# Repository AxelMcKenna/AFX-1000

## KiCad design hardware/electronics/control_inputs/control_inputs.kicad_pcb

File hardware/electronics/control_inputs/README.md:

# E18 digital input hub

This 64 × 54 mm, four-layer board connects all32 front button/selector inputs
and four external-profile rear/status inputs to three MCP23017-E/SO expanders.
It uses the corrected [F04 mapping](../../firmware/control-inputs.json), leaving
GPA7/GPB7 unconnected because the manufacturer specifies them as output-only.
It is a prototype subassembly. Pots, LED/display drivers, touch electrodes,
angle sensing and physical validation remain open.

The native schematic has15 circuit components. Its independently checked
netlist, all-severity ERC/DRC, schematic parity and open-connection checks pass.
The saved PCB has424 segments,62 through vias and a filled inner AGND plane.
These checks establish the saved connectivity and design-rule result; they
do not establish real scan latency, signal integrity, EMC/ESD or physical fit.

The PCB sits at layout(109,43), seat Z=12.1mm, above the E19 processor
carrier on four nominal4mm spacers. Its four Ø2.4mm mounting holes are board-
relative(4,4),(60,4),(4,50),(60,50). Matching E19 processor-carrier holes and copper
keepouts are implemented. The 2mm left shift clears the lower fixing bounds.
Spacer OD≤5.5mm,
screw/washer OD≤5.5mm and head height≤2mm are assembly limits with no selected
parts or engagement proof. The placement packet uses actual PCB courtyards,
connector expansion0.5mm, an11mm connector/harness height allocation,≤3mm
trimmed THT protrusion including solder and stated board/seat allowances.
The A05 housing model includes the routed E19 carrier, lower fixing heads/nuts
and the daughterboard allocations. Complete wiring paths, exact fixing parts
and final electronics fit remain open.

| Header | Connection |
| --- | --- |
| J1,2×8 | Front inputs0–13; pin order follows the routed fanout; pins15/16 ground |
| J2,2×8 | Front inputs14–27; pins15/16 ground |
| J3,1×5 | Ground,Scene9,Default/User,Back Spin,Vinyl Brake |
| J4,1×5 | Ground,Send/Return sense,manual bypass sense,ANALOG_OK,INPUT_READY |
| J5,1×5 | Ground,shared MCU3.3V,SCL,SDA,CONTROL_RESET_N |

Use the [exported connector map](generated/connector-map.csv) for every pin and
logical control ID. J1/J2 alternate A-side reverse order with B-side forward
order; do not wire them as consecutive logical inputs. The connectors are
engineering pin-header footprints. Production connector, mating cable,
retention and polarity/keying selections remain unfinished.

**Connect J4 only with `PROFILE=external`.** Onboard firmware makes its GPA0..3
unused low outputs; leave J4 unplugged for onboard-codec bring-up. External
ANALOG_OK and INPUT_READY receive47kΩ/270kΩ pull-downs on this board and no
internal pull-ups. This implements the receiving loads required by E09/E11.
Both active-low rear switch inputs use the expander's configured pull-ups.

J5 reset is D0/CODEC_RUN externally or D27 onboard. R1 adds a receiving100kΩ
pull-down; this replaces the earlier prospective onboard reset pull-up.
F04 drives reset low then high and verifies direction/pull-up/output-latch
readback before accepting controls. Missing-drive, partial-power, leakage and
reset transients still need hardware qualification. A shared3.3V supply is
required; never power this board's logic from5V or join independent3.3V outputs.

There are no I²C pull-ups on E18. E09 R1/R2 supply the single2kΩ pair for the
external profile. Onboard bench bring-up needs an equivalent external pair.
Include fixed module pull-ups in the total bus load and measure rise time,
capacitance, ringing and actual scan cadence before accepting400kHz operation.
All switch leads remain inside the enclosure; system-level ESD/EMI provisions
and harness qualification are unfinished.

Regenerate and verify with the root [uv environment](../../../README.md#python-tooling)
and KiCad10.0.7:

```sh
uv run --locked python -m hardware.electronics.control_inputs.generate
uv run --locked python -m hardware.electronics.control_inputs.board --kicad-cli /path/to/kicad-cli
uv run --locked python -m hardware.electronics.control_inputs.verify --kicad-cli /path/to/kicad-cli
uv run --locked python -m hardware.cad.standalone
uv run --locked python -m hardware.cad.render --openscad /path/to/openscad
```

`board.py` uses explicit GPIO fanouts and a conservative grid-routing aid for
the remaining slow digital nets. Native KiCad DRC/parity checks the resulting
saved copper. `verify.py` independently declares all15 component contracts,
checks F04 logical/physical input mapping and NC-pad isolation, audits SOIC
pad numbering/positions, re-exports E09/E11 interfaces, and produces the
[verification record](generated/verification.json) and
[PCB placement packet](generated/placement.json). It uses shared parser and
transform helpers from E07; it does not import this board's circuit specification.

The MCP source is Microchip
[DS20001952D](https://ww1.microchip.com/downloads/aemDocuments/documents/APID/ProductDocuments/DataSheets/MCP23017-Data-Sheet-DS20001952.pdf).
Standard KiCad footprints are embedded in the board and hashed in the record.
Full manufacturer land-pattern/stencil approval, exact passive/connector MPNs,
fabrication stackup and physical performance are still pending. This board
does not complete the standalone unit or authorize a complete fabrication run.

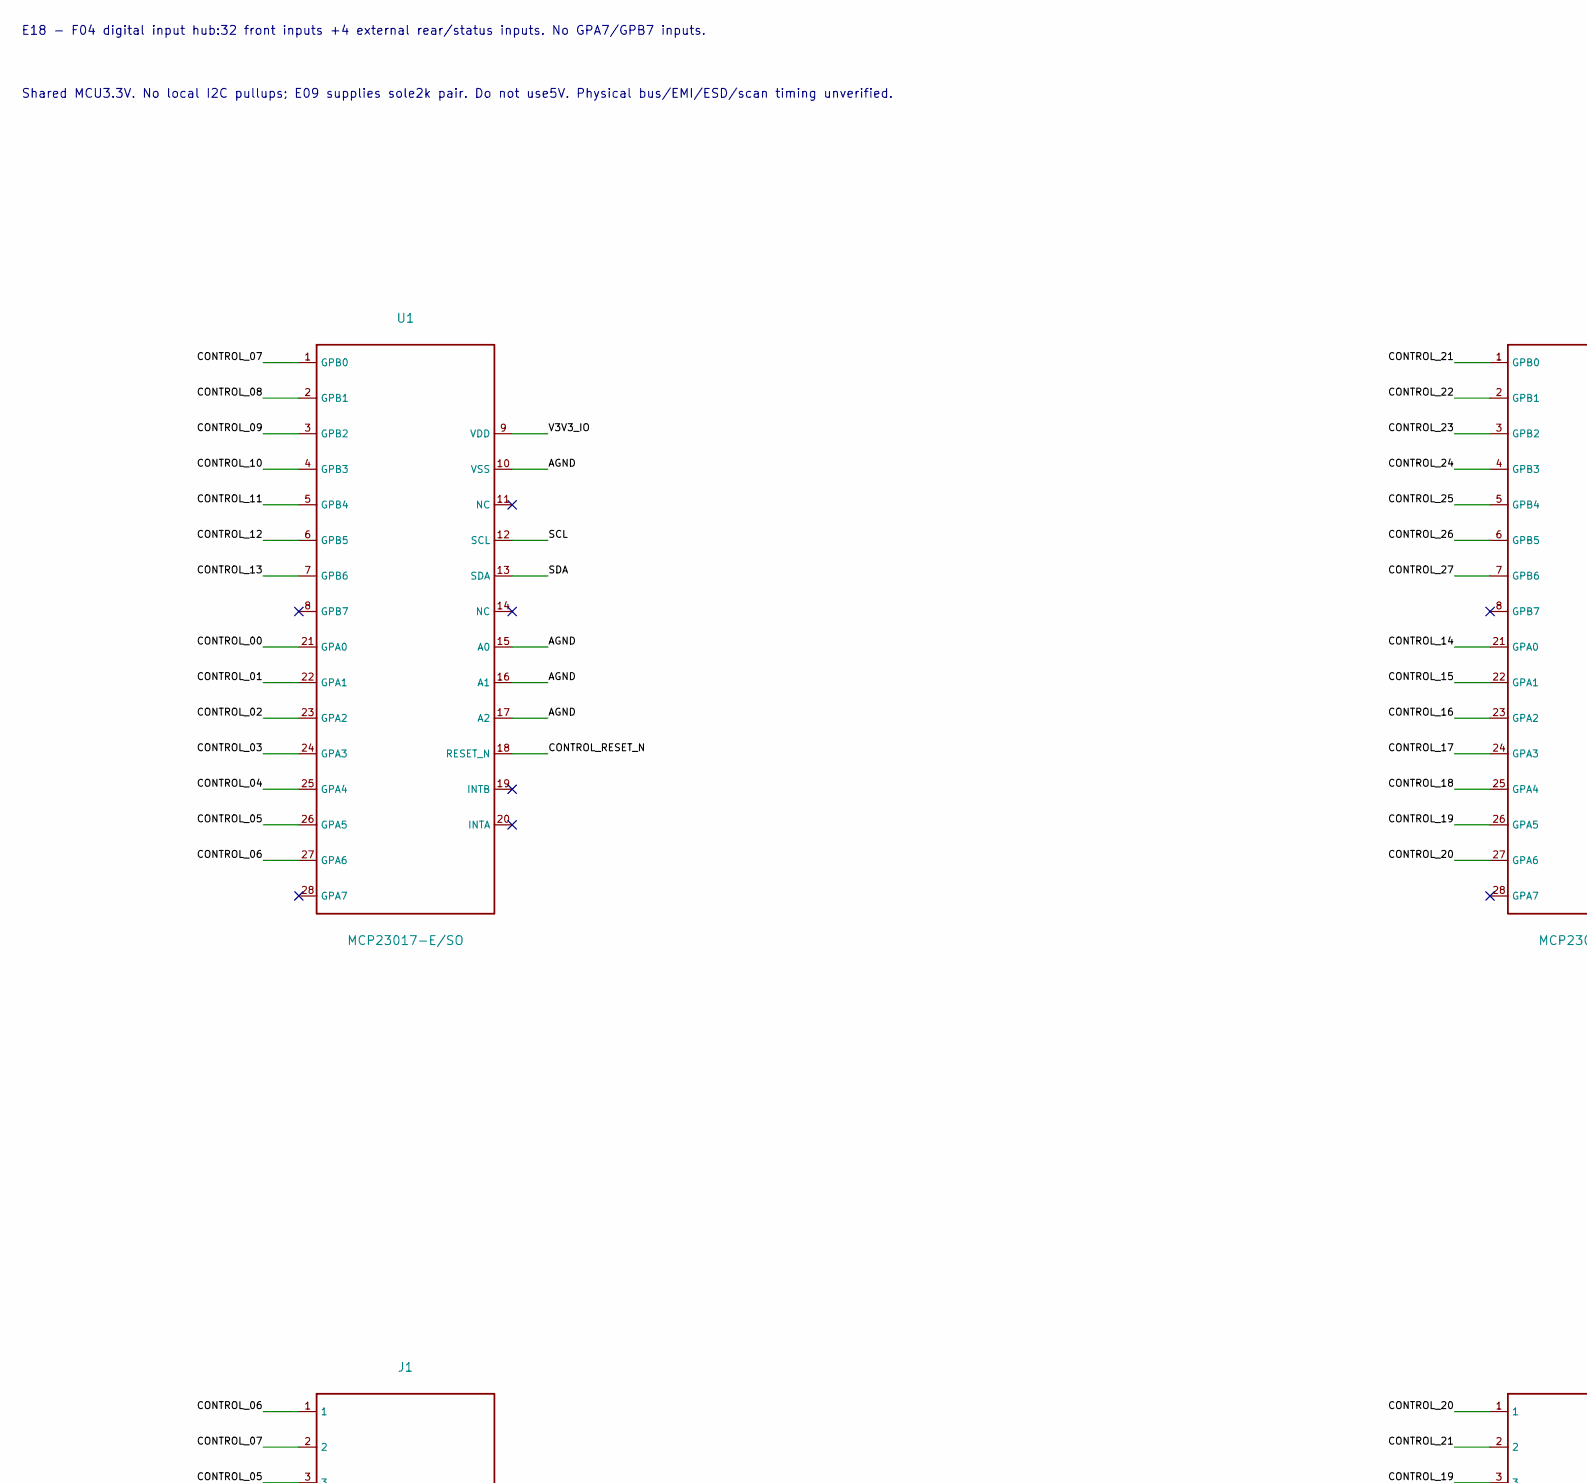
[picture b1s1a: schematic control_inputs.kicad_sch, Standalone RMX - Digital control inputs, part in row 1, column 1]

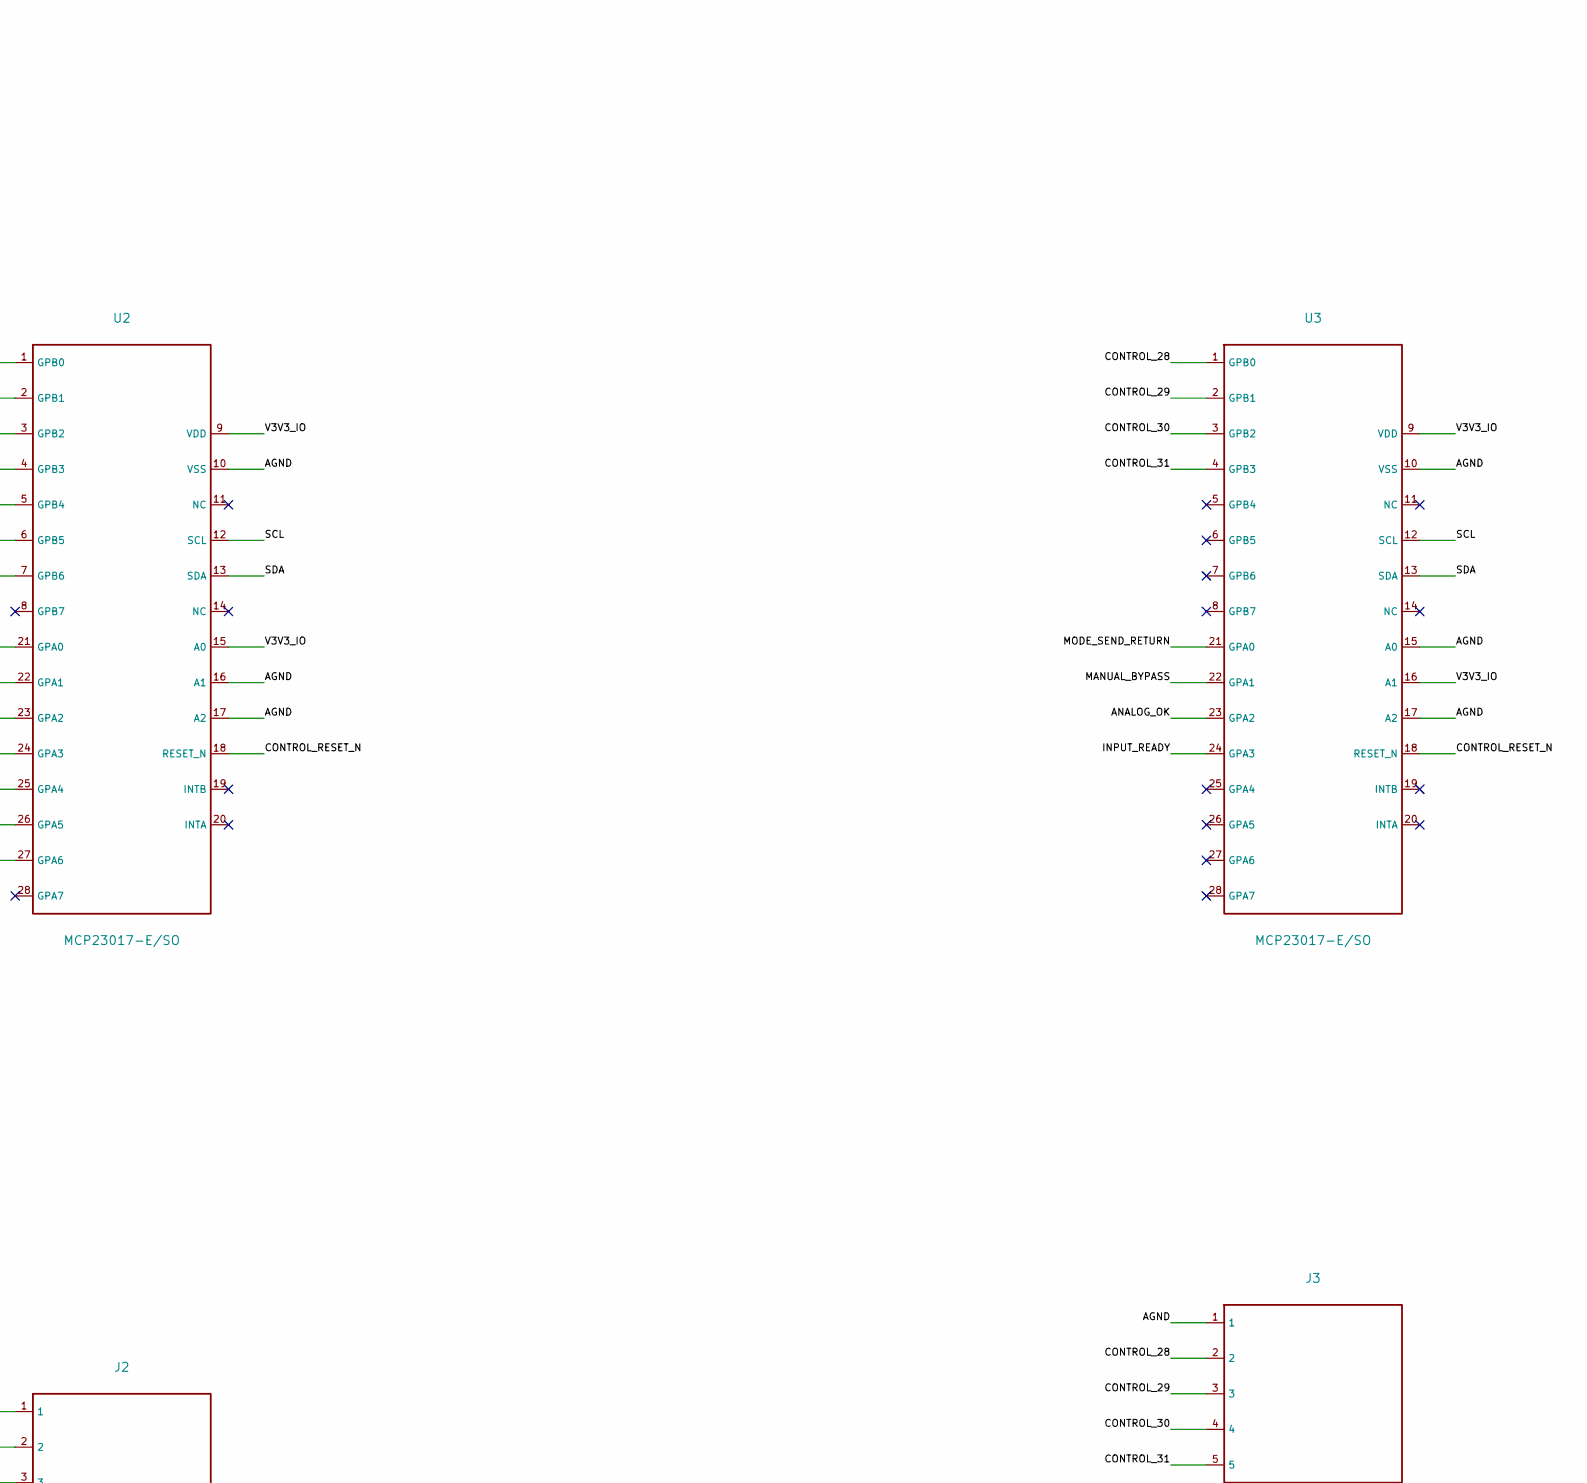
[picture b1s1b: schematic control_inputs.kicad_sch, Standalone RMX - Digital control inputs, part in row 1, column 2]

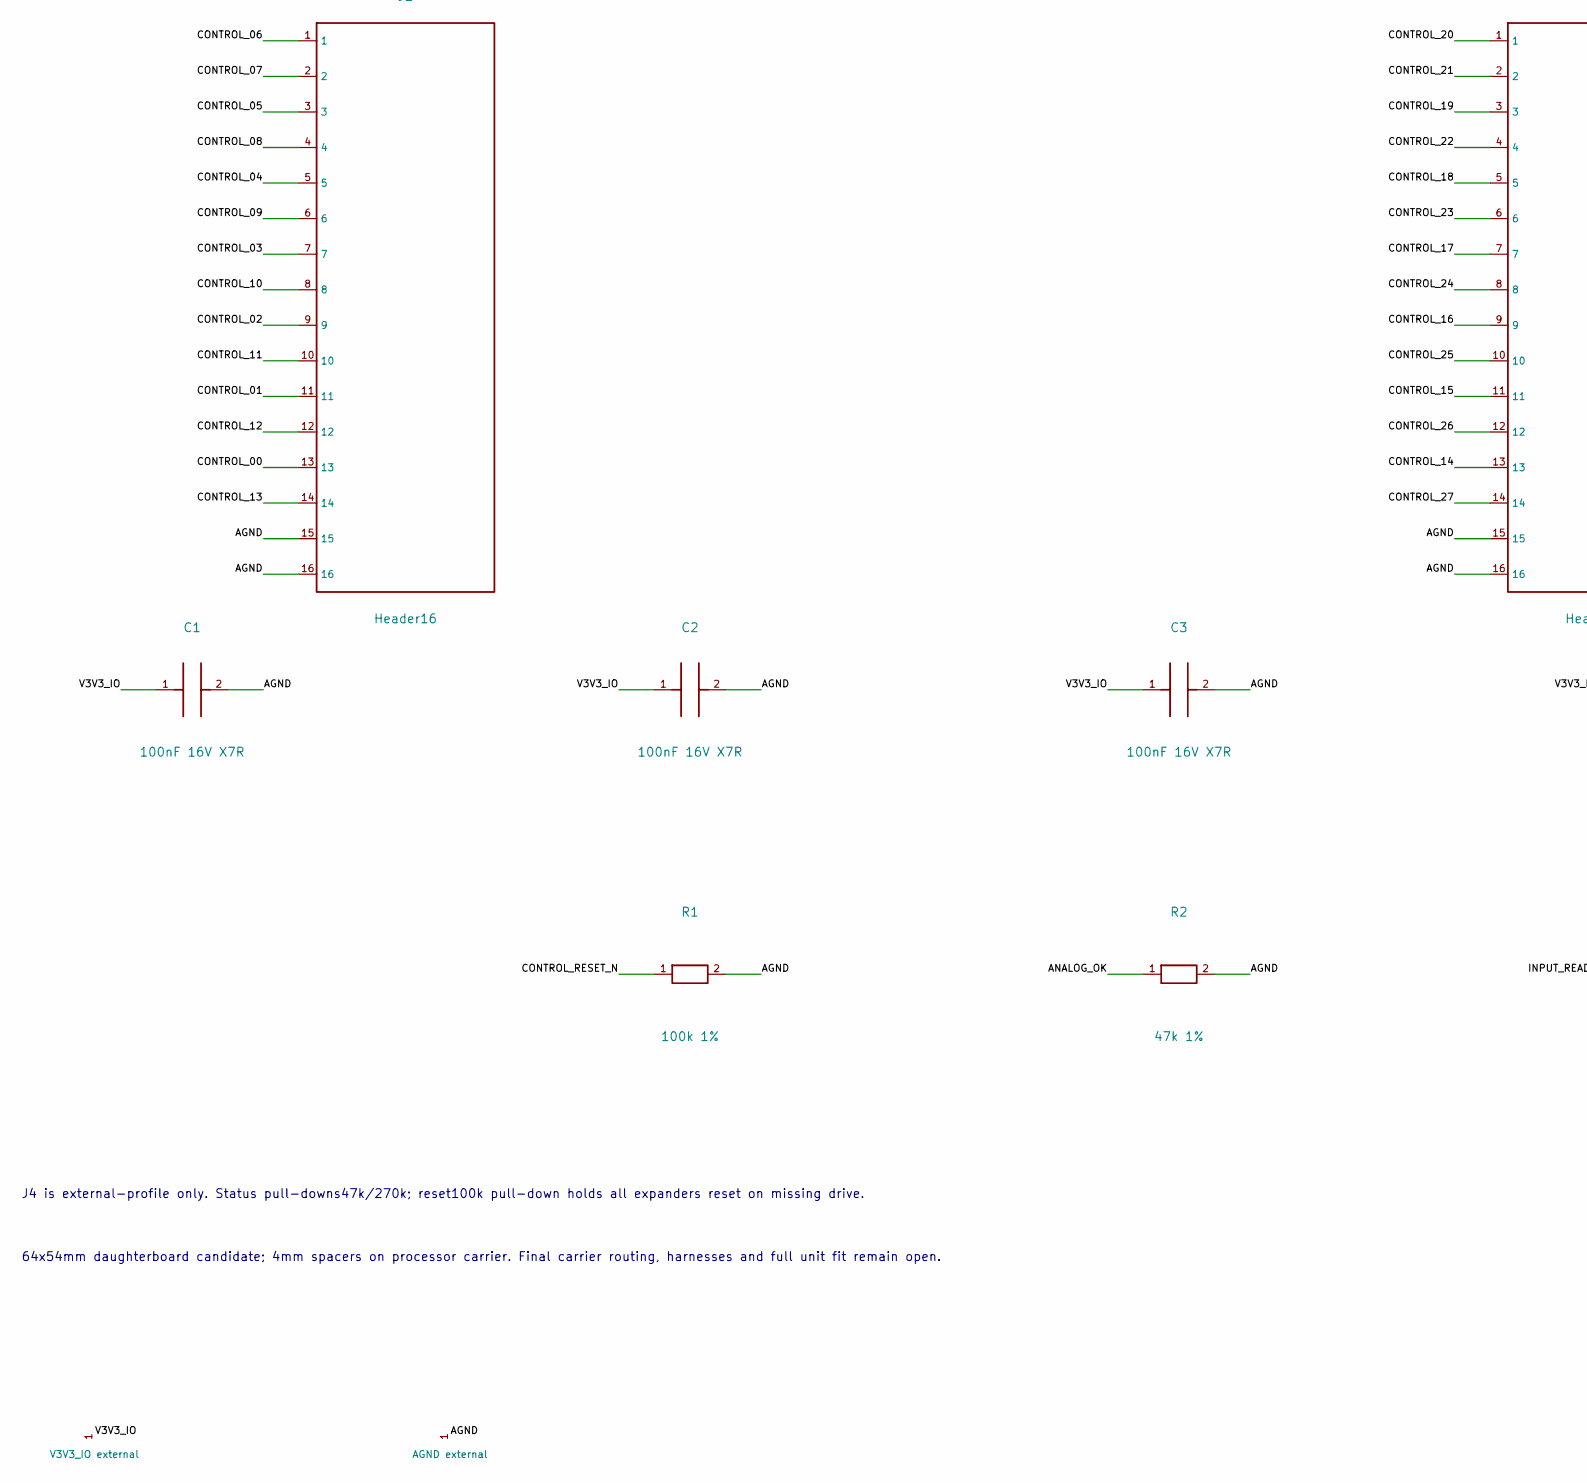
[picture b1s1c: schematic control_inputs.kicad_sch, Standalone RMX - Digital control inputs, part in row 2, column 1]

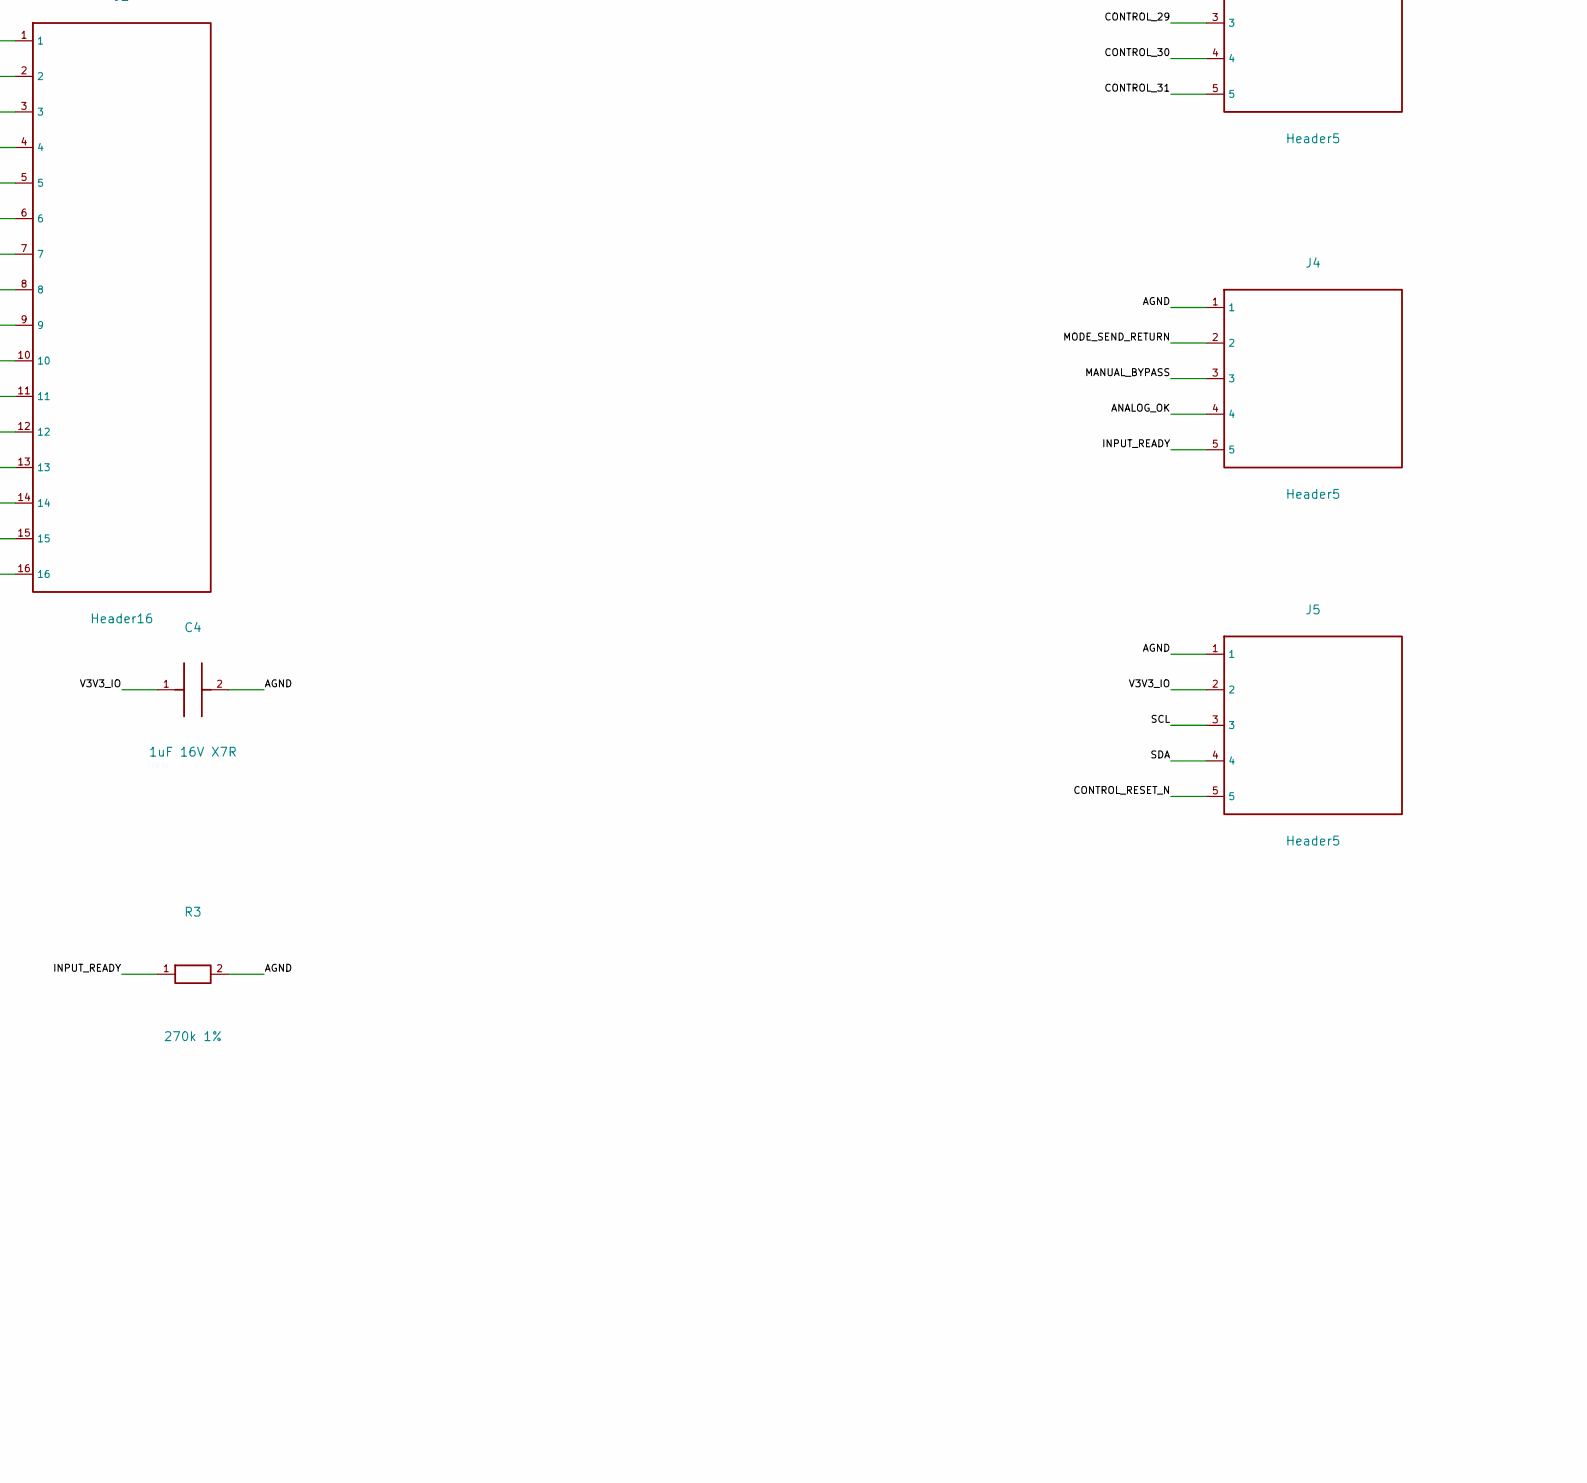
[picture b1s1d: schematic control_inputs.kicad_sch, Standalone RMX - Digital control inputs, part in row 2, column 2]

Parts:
C1, C2, C3: 100nF 16V X7R; C_0805_2012Metric
C4: 1uF 16V X7R; C_0805_2012Metric
J1, J2: Header16; PinHeader_2x08_P2.54mm_Vertical
J3, J4, J5: Header5; PinHeader_1x05_P2.54mm_Vertical
R1: 100k 1%; R_0805_2012Metric
R2: 47k 1%; R_0805_2012Metric
R3: 270k 1%; R_0805_2012Metric
U1, U2, U3: MCP23017-E/SO; SOIC-28W_7.5x17.9mm_P1.27mm

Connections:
/AGND: C1.2, C2.2, C3.2, C4.2, J1.15, J1.16, J2.15, J2.16, J3.1, J4.1, J5.1, R1.2, R2.2, R3.2, U1.10 (VSS), U1.15 (A0), U1.16 (A1), U1.17 (A2), U2.10 (VSS), U2.16 (A1), U2.17 (A2), U3.10 (VSS), U3.15 (A0), U3.17 (A2)
/ANALOG_OK: J4.4, R2.1, U3.23 (GPA2)
/CONTROL_00: J1.13, U1.21 (GPA0)
/CONTROL_01: J1.11, U1.22 (GPA1)
/CONTROL_02: J1.9, U1.23 (GPA2)
/CONTROL_03: J1.7, U1.24 (GPA3)
/CONTROL_04: J1.5, U1.25 (GPA4)
/CONTROL_05: J1.3, U1.26 (GPA5)
/CONTROL_06: J1.1, U1.27 (GPA6)
/CONTROL_07: J1.2, U1.1 (GPB0)
/CONTROL_08: J1.4, U1.2 (GPB1)
/CONTROL_09: J1.6, U1.3 (GPB2)
/CONTROL_10: J1.8, U1.4 (GPB3)
/CONTROL_11: J1.10, U1.5 (GPB4)
/CONTROL_12: J1.12, U1.6 (GPB5)
/CONTROL_13: J1.14, U1.7 (GPB6)
/CONTROL_14: J2.13, U2.21 (GPA0)
/CONTROL_15: J2.11, U2.22 (GPA1)
/CONTROL_16: J2.9, U2.23 (GPA2)
/CONTROL_17: J2.7, U2.24 (GPA3)
/CONTROL_18: J2.5, U2.25 (GPA4)
/CONTROL_19: J2.3, U2.26 (GPA5)
/CONTROL_20: J2.1, U2.27 (GPA6)
/CONTROL_21: J2.2, U2.1 (GPB0)
/CONTROL_22: J2.4, U2.2 (GPB1)
/CONTROL_23: J2.6, U2.3 (GPB2)
/CONTROL_24: J2.8, U2.4 (GPB3)
/CONTROL_25: J2.10, U2.5 (GPB4)
/CONTROL_26: J2.12, U2.6 (GPB5)
/CONTROL_27: J2.14, U2.7 (GPB6)
/CONTROL_28: J3.2, U3.1 (GPB0)
/CONTROL_29: J3.3, U3.2 (GPB1)
/CONTROL_30: J3.4, U3.3 (GPB2)
/CONTROL_31: J3.5, U3.4 (GPB3)
/CONTROL_RESET_N: J5.5, R1.1, U1.18 (RESET_N), U2.18 (RESET_N), U3.18 (RESET_N)
/INPUT_READY: J4.5, R3.1, U3.24 (GPA3)
/MANUAL_BYPASS: J4.3, U3.22 (GPA1)
/MODE_SEND_RETURN: J4.2, U3.21 (GPA0)
/SCL: J5.3, U1.12 (SCL), U2.12 (SCL), U3.12 (SCL)
/SDA: J5.4, U1.13 (SDA), U2.13 (SDA), U3.13 (SDA)
/V3V3_IO: C1.1, C2.1, C3.1, C4.1, J5.2, U1.9 (VDD), U2.9 (VDD), U2.15 (A0), U3.9 (VDD), U3.16 (A1)

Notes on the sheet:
E18 - F04 digital input hub:32 front inputs +4 external rear/status inputs. No GPA7/GPB7 inputs.
Shared MCU3.3V. No local I2C pullups; E09 supplies sole2k pair. Do not use5V. Physical bus/EMI/ESD/scan timing unverified.
J4 is external-profile only. Status pull-downs47k/270k; reset100k pull-down holds all expanders reset on missing drive.
64x54mm daughterboard candidate; 4mm spacers on processor carrier. Final carrier routing, harnesses and full unit fit remain open.

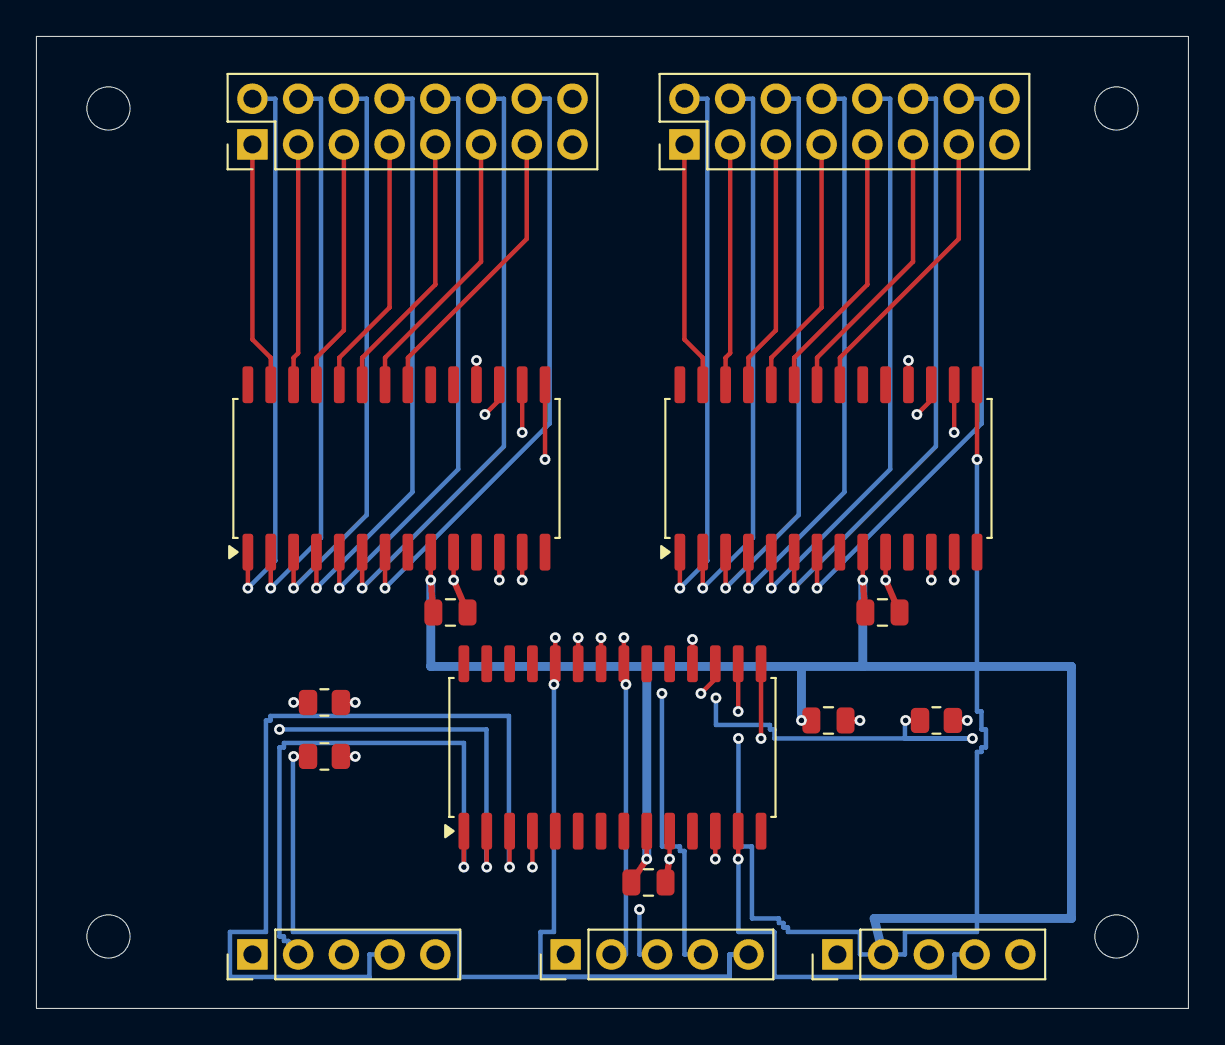
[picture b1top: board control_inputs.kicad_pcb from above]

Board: 4 copper layers, 64.0 x 54.0 mm, 19 parts (0 on the bottom side), 41 nets.

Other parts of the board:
H1, H2, H3, H4: M2_CLEARANCE; M2_Clearance

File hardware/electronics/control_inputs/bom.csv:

Reference,Part_or_value,Footprint,Source,Note
U1,MCP23017-E/SO,Package_SO:SOIC-28W_7.5x17.9mm_P1.27mm,https://ww1.microchip.com/downloads/aemDocuments/documents/A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,7-bit address0x20; GPA7/GPB7 unused output-only pins; F04 required
U2,MCP23017-E/SO,Package_SO:SOIC-28W_7.5x17.9mm_P1.27mm,https://ww1.microchip.com/downloads/aemDocuments/documents/A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,7-bit address0x21; GPA7/GPB7 unused output-only pins; F04 required
U3,MCP23017-E/SO,Package_SO:SOIC-28W_7.5x17.9mm_P1.27mm,https://ww1.microchip.com/downloads/aemDocuments/documents/A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,7-bit address0x22; GPA7/GPB7 unused output-only pins; F04 required
J1,Header16,Connector_PinHeader_2.54mm:PinHeader_2x08_P2.54mm_Vertical,,"Two-row bench header; pin order follows routing, not logical index. Production connector/harness unselected."
J2,Header16,Connector_PinHeader_2.54mm:PinHeader_2x08_P2.54mm_Vertical,,"Two-row bench header; pin order follows routing, not logical index. Production connector/harness unselected."
J3,Header5,Connector_PinHeader_2.54mm:PinHeader_1x05_P2.54mm_Vertical,,"Scene9, settings and release endpoints; close active-low inputs to ground."
J4,Header5,Connector_PinHeader_2.54mm:PinHeader_1x05_P2.54mm_Vertical,,Connect only with PROFILE=external. Onboard firmware configures GPA0..3 as unused low outputs; leave J4 unplugged.
J5,Header5,Connector_PinHeader_2.54mm:PinHeader_1x05_P2.54mm_Vertical,,"Shared MCU3.3V only; external reset=D0/CODEC_RUN, onboard=D27. I2C pullups external: E09 has sole2k pair."
R1,100k 1%,Resistor_SMD:R_0805_2012Metric,,Receiving-end pull-down; do not enable status pull-ups in firmware.
R2,47k 1%,Resistor_SMD:R_0805_2012Metric,,Receiving-end pull-down; do not enable status pull-ups in firmware.
R3,270k 1%,Resistor_SMD:R_0805_2012Metric,,Receiving-end pull-down; do not enable status pull-ups in firmware.
C1,100nF 16V X7R,Capacitor_SMD:C_0805_2012Metric,,Local bypass per IC plus input bulk; effective capacitance and exact MPN require qualification.
C2,100nF 16V X7R,Capacitor_SMD:C_0805_2012Metric,,Local bypass per IC plus input bulk; effective capacitance and exact MPN require qualification.
C3,100nF 16V X7R,Capacitor_SMD:C_0805_2012Metric,,Local bypass per IC plus input bulk; effective capacitance and exact MPN require qualification.
C4,1uF 16V X7R,Capacitor_SMD:C_0805_2012Metric,,Local bypass per IC plus input bulk; effective capacitance and exact MPN require qualification.
